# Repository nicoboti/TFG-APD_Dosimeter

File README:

Hola, bienvenidos a mi repositorio.

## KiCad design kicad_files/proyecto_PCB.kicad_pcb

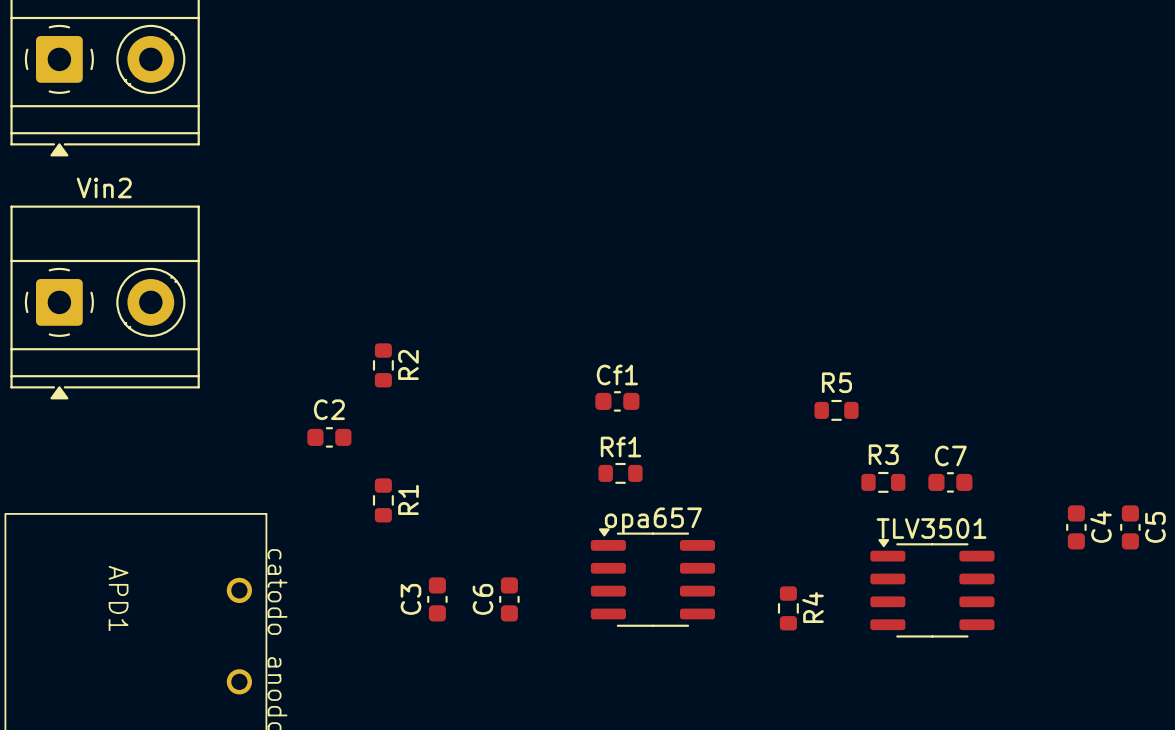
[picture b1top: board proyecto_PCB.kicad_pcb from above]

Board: 2 copper layers, 18 parts (0 on the bottom side), 8 nets, no tracks yet.

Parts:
APD1: APD_S8664-1010
C2: 0.1 muF; C_0603_1608Metric
C3: 10 nF; C_0603_1608Metric
C4: 2.2muF; C_0603_1608Metric
C5, C7: 100nF; C_0603_1608Metric
C6: 100 nF; C_0603_1608Metric
Cf1: 0.55 pF; C_0603_1608Metric
R1: 5 MΩ; R_0603_1608Metric
R2: 10 MΩ; R_0603_1608Metric
R3: 1 kΩ; R_0603_1608Metric
R4: 50 Ω; R_0603_1608Metric
R5: 47 kΩ; R_0603_1608Metric
Rf1: 200 kΩ; R_0603_1608Metric
TLV3501: SOIC-8_3.9x4.9mm_P1.27mm
Vin1, Vin2: Terminal_2pines_5.08mm
opa657: opa657

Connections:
+5V: C4.1, C5.1, R5.2, TLV3501.7 (V+), Vin1.2, opa657.7 (V+)
+400V: R2.1, Vin2.2
GND: APD1.1 (A), C2.1, C3.1, C4.2, C5.2, C6.1, C7.2, R4.2, TLV3501.4 (V-), Vin1.1, Vin2.1, opa657.3 (IN+), opa657.4 (V-)
unnamed: APD1.2 (K), C3.2, C6.2, Cf1.1, R1.2, Rf1.1, opa657.2 (IN-)
unnamed: C2.2, R1.1, R2.2
unnamed: C7.1, R3.2
unnamed: Cf1.2, R4.1, Rf1.2, TLV3501.3 (+), opa657.6 (Vout)
unnamed: R3.1, R5.1, TLV3501.2 (-)

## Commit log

2025-09-05 diseño Kicad
2025-09-05 Diseño LTSpice
2025-09-05 Rename README.md to README
2025-09-08 Primera versión organizada (Python, KiCad, LTspice sin archivos grandes)
2025-09-08 Renombro carpeta y añado el documento del TFG a docs
2025-09-08 Added new folders & files
